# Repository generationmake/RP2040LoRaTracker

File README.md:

# RP2040LoRaTracker
Tracker with a Raspberry Pi RP2040, an AI-Thinker Ra-01 LoRa Module and an u-Blox GNSS receiver

## Firmware
* [ArduinoLoRaAPRSTracker](https://github.com/generationmake/ArduinoLoRaAPRSTracker): This is the default firmware for this board. It enables all basic functions as a ham radio LoRaAPRSTracker

## Antennas

### LoRa antenna (AE1)

SMA connector, 50 Ohm, for 433 MHz LoRa antenna.

### GNSS antenna (AE2)

U.FL connector, 50 Ohm, for GNSS antenna.

## Pinout

### USB (J1)

Micro-USB connector, connected to the RP2040 ant to charge the battery.

### I2C (J2)

compatible to the Sparkfun qwiic standard (https://www.sparkfun.com/qwiic). JST SH 1mm 4-pin.

| pin number | signal        |
|:----------:|:-------------:|
| 1          | GND           |
| 2          | +3V3          |
| 3          | I2C_SDA       |
| 4          | I2C_SCL       |

## Switches

### Reset (SW1)

push button to reset RP2040.

### Boot (SW2)

push button to set RP2040 to boot mode.

### on/off (SW3)

sliding switch to power board from battery.

## enclosure

There exists a 3D printable enclosure to encapsulate the PCB.

## PCB

### Top

### Bottom

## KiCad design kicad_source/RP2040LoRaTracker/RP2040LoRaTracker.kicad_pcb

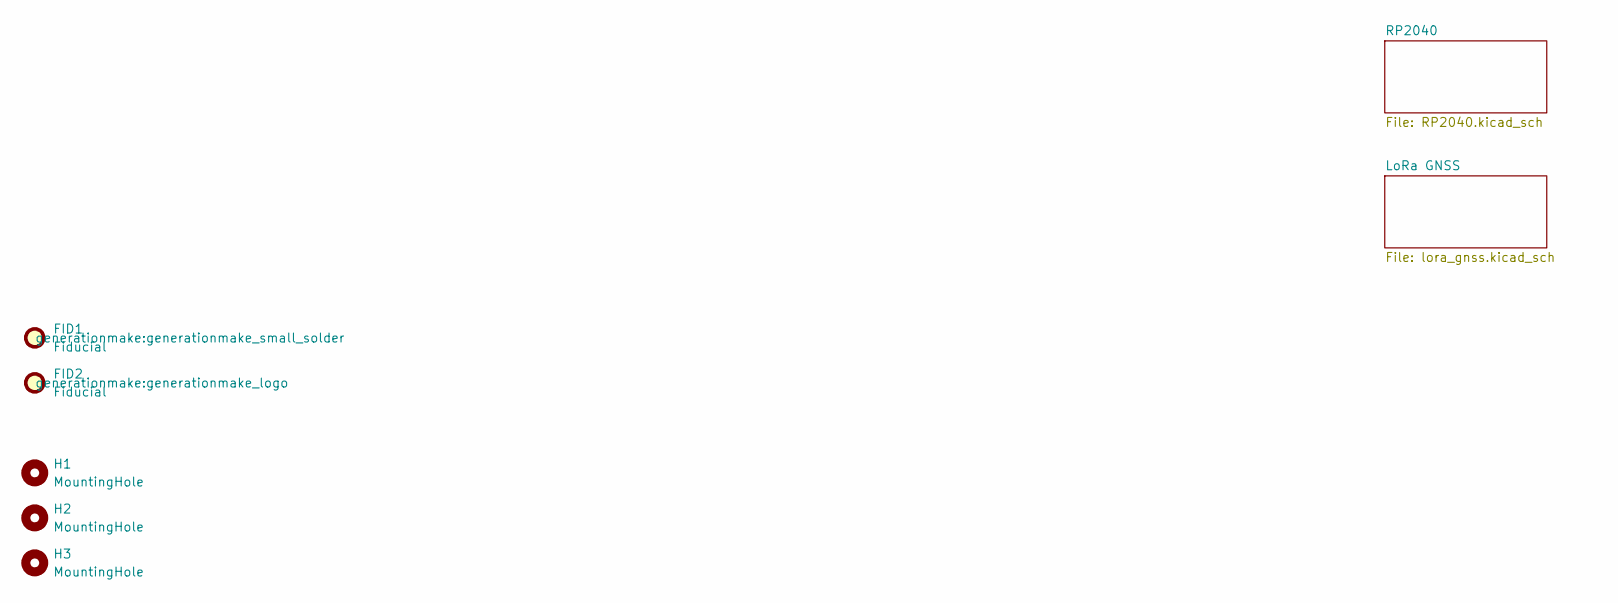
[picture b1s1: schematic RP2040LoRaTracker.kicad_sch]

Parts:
FID1: Fiducial; generationmake_small_solder
FID2: Fiducial; generationmake_logo
H1, H2, H3: MountingHole; MountingHole_2.2mm_M2

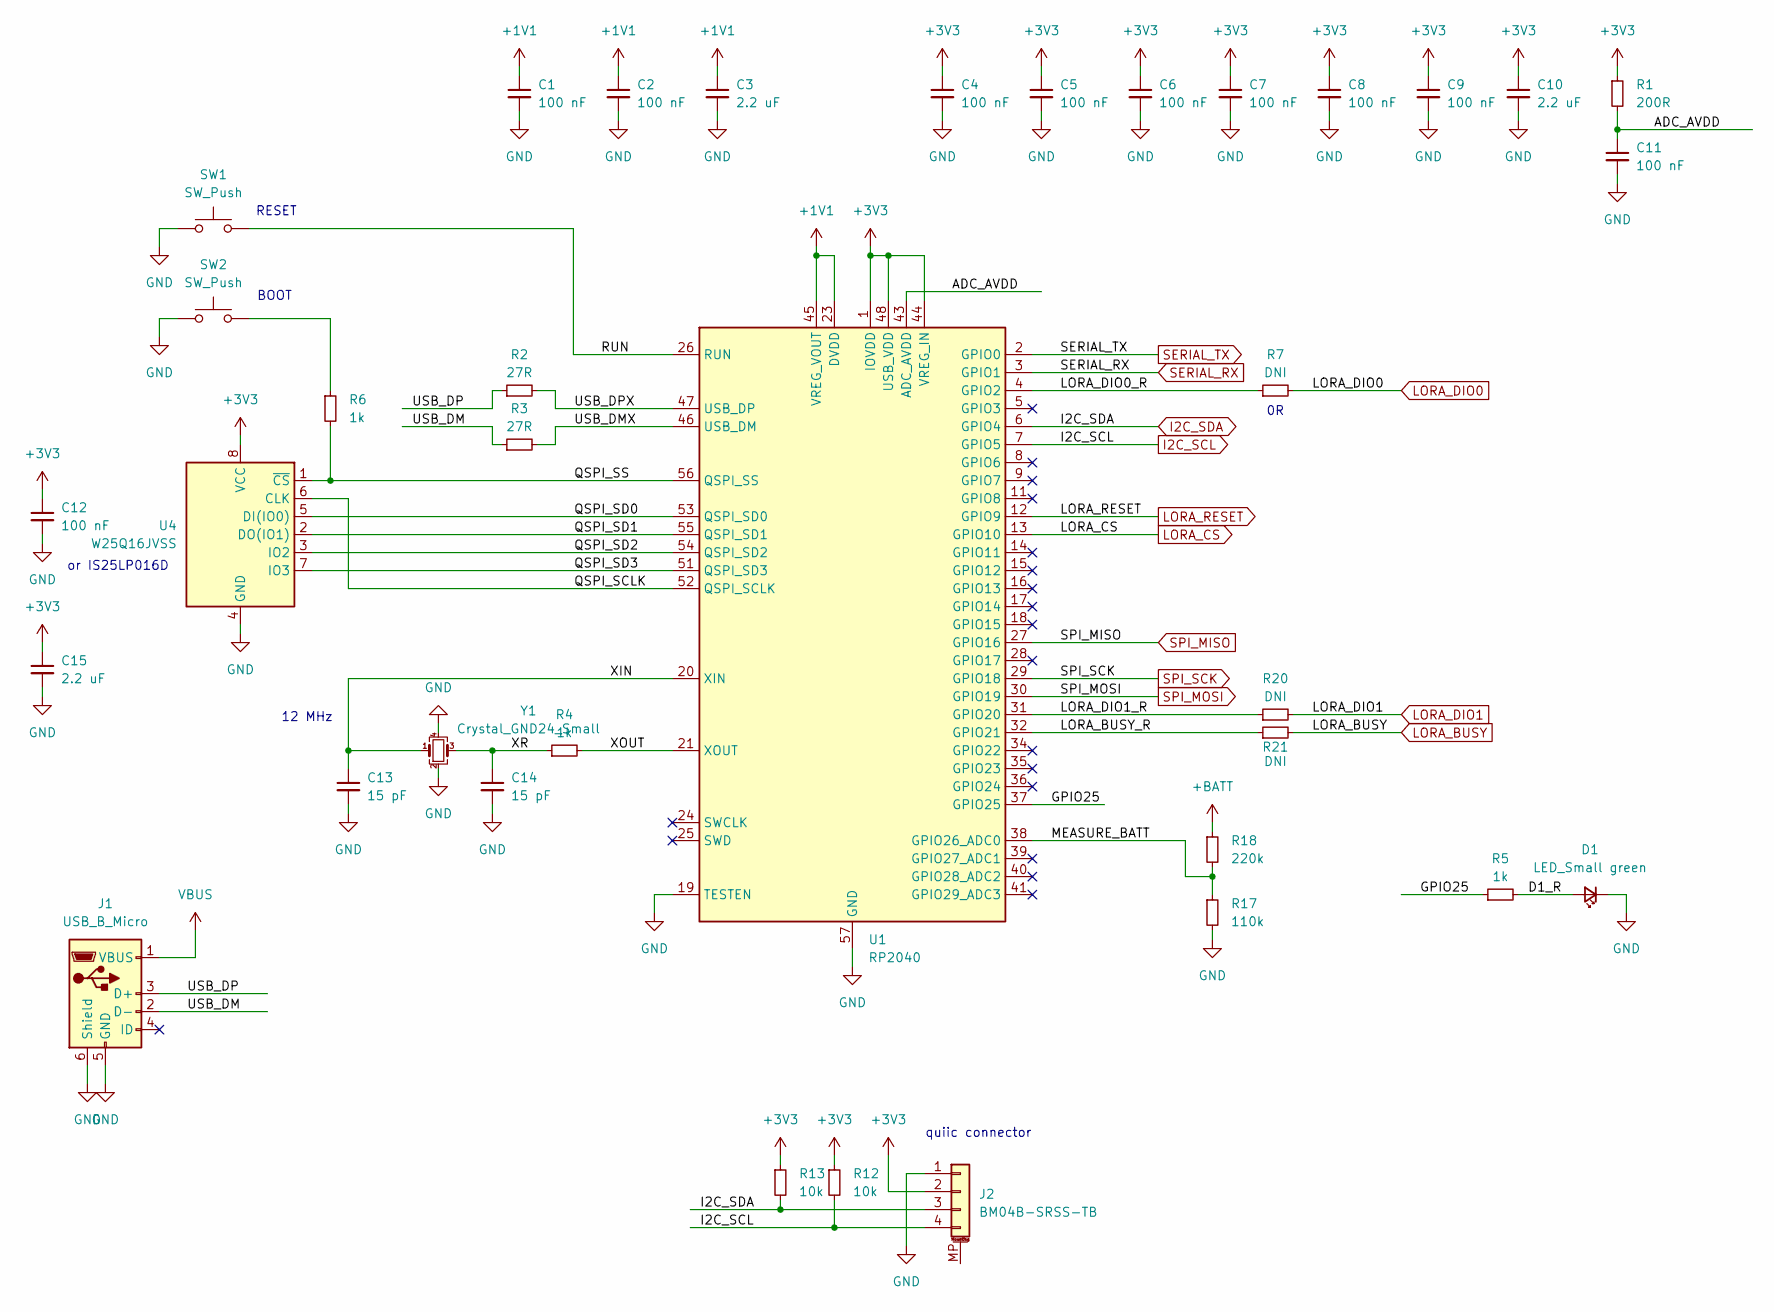
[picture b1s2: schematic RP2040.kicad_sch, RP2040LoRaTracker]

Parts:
C1, C2, C4, C5, C6, C7, C8, C9, C11, C12: 100 nF; C_0603_1608Metric
C3, C10, C15: 2.2 uF; C_0603_1608Metric
C13, C14: 15 pF; C_0603_1608Metric
D1: LED_Small green; LED_0603_1608Metric
J1: USB_B_Micro; USB_Micro-B_Molex_47346-0001
J2: BM04B-SRSS-TB; JST_SH_BM04B-SRSS-TB_1x04-1MP_P1.00mm_Vertical
R1: 200R; R_0603_1608Metric
R2, R3: 27R; R_0603_1608Metric
R4, R5, R6: 1k; R_0603_1608Metric
R7, R20, R21: DNI; R_0603_1608Metric
R12, R13: 10k; R_0603_1608Metric
R17: 110k; R_0603_1608Metric
R18: 220k; R_0603_1608Metric
SW1, SW2: SW_Push; SW_Tactile_SPST_NO_Straight_CK_PTS636Sx25SMTRLFS
U1: RP2040; QFN-56-1EP_7x7mm_P0.4mm_EP3.2x3.2mm
U4: W25Q16JVSS; SOIC-8_5.275x5.275mm_P1.27mm
Y1: Crystal_GND24_Small; Crystal_SMD_3225-4Pin_3.2x2.5mm

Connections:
+1V1: C1.1, C2.1, C3.1, U1.23 (DVDD), U1.45 (VREG_VOUT), U1.50 (DVDD)
+3V3: C4.1, C5.1, C6.1, C7.1, C8.1, C9.1, C10.1, C12.1, C15.1, J2.2, R1.1, R12.1, R13.1, U1.1 (IOVDD), U1.10 (IOVDD), U1.22 (IOVDD), U1.33 (IOVDD), U1.42 (IOVDD), U1.44 (VREG_IN), U1.48 (USB_VDD), U1.49 (IOVDD), U4.8 (VCC); also elsewhere on the board
+BATT: R18.1; also elsewhere on the board
/RP2040/ADC_AVDD: C11.1, R1.2, U1.43 (ADC_AVDD)
/RP2040/D1_R: D1.2 (A), R5.2
/RP2040/GPIO25: R5.1, U1.37 (GPIO25)
/RP2040/LORA_BUSY_R: R21.1, U1.32 (GPIO21)
/RP2040/LORA_DIO0_R: R7.1, U1.4 (GPIO2)
/RP2040/LORA_DIO1_R: R20.1, U1.31 (GPIO20)
/RP2040/MEASURE_BATT: R17.1, R18.2, U1.38 (GPIO26_ADC0)
/RP2040/QSPI_SCLK: U1.52 (QSPI_SCLK), U4.6 (CLK)
/RP2040/QSPI_SD0: U1.53 (QSPI_SD0), U4.5 (DI(IO0))
/RP2040/QSPI_SD1: U1.55 (QSPI_SD1), U4.2 (DO(IO1))
/RP2040/QSPI_SD2: U1.54 (QSPI_SD2), U4.3 (IO2)
/RP2040/QSPI_SD3: U1.51 (QSPI_SD3), U4.7 (IO3)
/RP2040/QSPI_SS: R6.2, U1.56 (QSPI_SS), U4.1 (~CS)
/RP2040/RUN: SW1.2, U1.26 (RUN)
/RP2040/USB_DM: J1.2 (D-), R3.1
/RP2040/USB_DMX: R3.2, U1.46 (USB_DM)
/RP2040/USB_DP: J1.3 (D+), R2.1
/RP2040/USB_DPX: R2.2, U1.47 (USB_DP)
/RP2040/XIN: C13.1, U1.20 (XIN), Y1.1
/RP2040/XOUT: R4.2, U1.21 (XOUT)
/RP2040/XR: C14.1, R4.1, Y1.3
GND: C1.2, C2.2, C3.2, C4.2, C5.2, C6.2, C7.2, C8.2, C9.2, C10.2, C11.2, C12.2, C13.2, C14.2, C15.2, D1.1 (K), J1.5 (GND), J1.6 (Shield), J2.1, R17.2, SW1.1, SW2.1, U1.19 (TESTEN), U1.57 (GND), U4.4 (GND), Y1.2, Y1.4; also elsewhere on the board
I2C_SCL: J2.4, R12.2, U1.7 (GPIO5); also elsewhere on the board
I2C_SDA: J2.3, R13.2, U1.6 (GPIO4); also elsewhere on the board
LORA_BUSY: R21.2; also elsewhere on the board
LORA_CS: U1.13 (GPIO10); also elsewhere on the board
LORA_DIO0: R7.2; also elsewhere on the board
LORA_DIO1: R20.2; also elsewhere on the board
LORA_RESET: U1.12 (GPIO9); also elsewhere on the board
unnamed: R6.1, SW2.2
SERIAL_RX: U1.3 (GPIO1); also elsewhere on the board
SERIAL_TX: U1.2 (GPIO0); also elsewhere on the board
SPI_MISO: U1.27 (GPIO16); also elsewhere on the board
SPI_MOSI: U1.30 (GPIO19); also elsewhere on the board
SPI_SCK: U1.29 (GPIO18); also elsewhere on the board
VBUS: J1.1 (VBUS); also elsewhere on the board

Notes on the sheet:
12 MHz
or IS25LP016D
quiic connector
BOOT
RESET

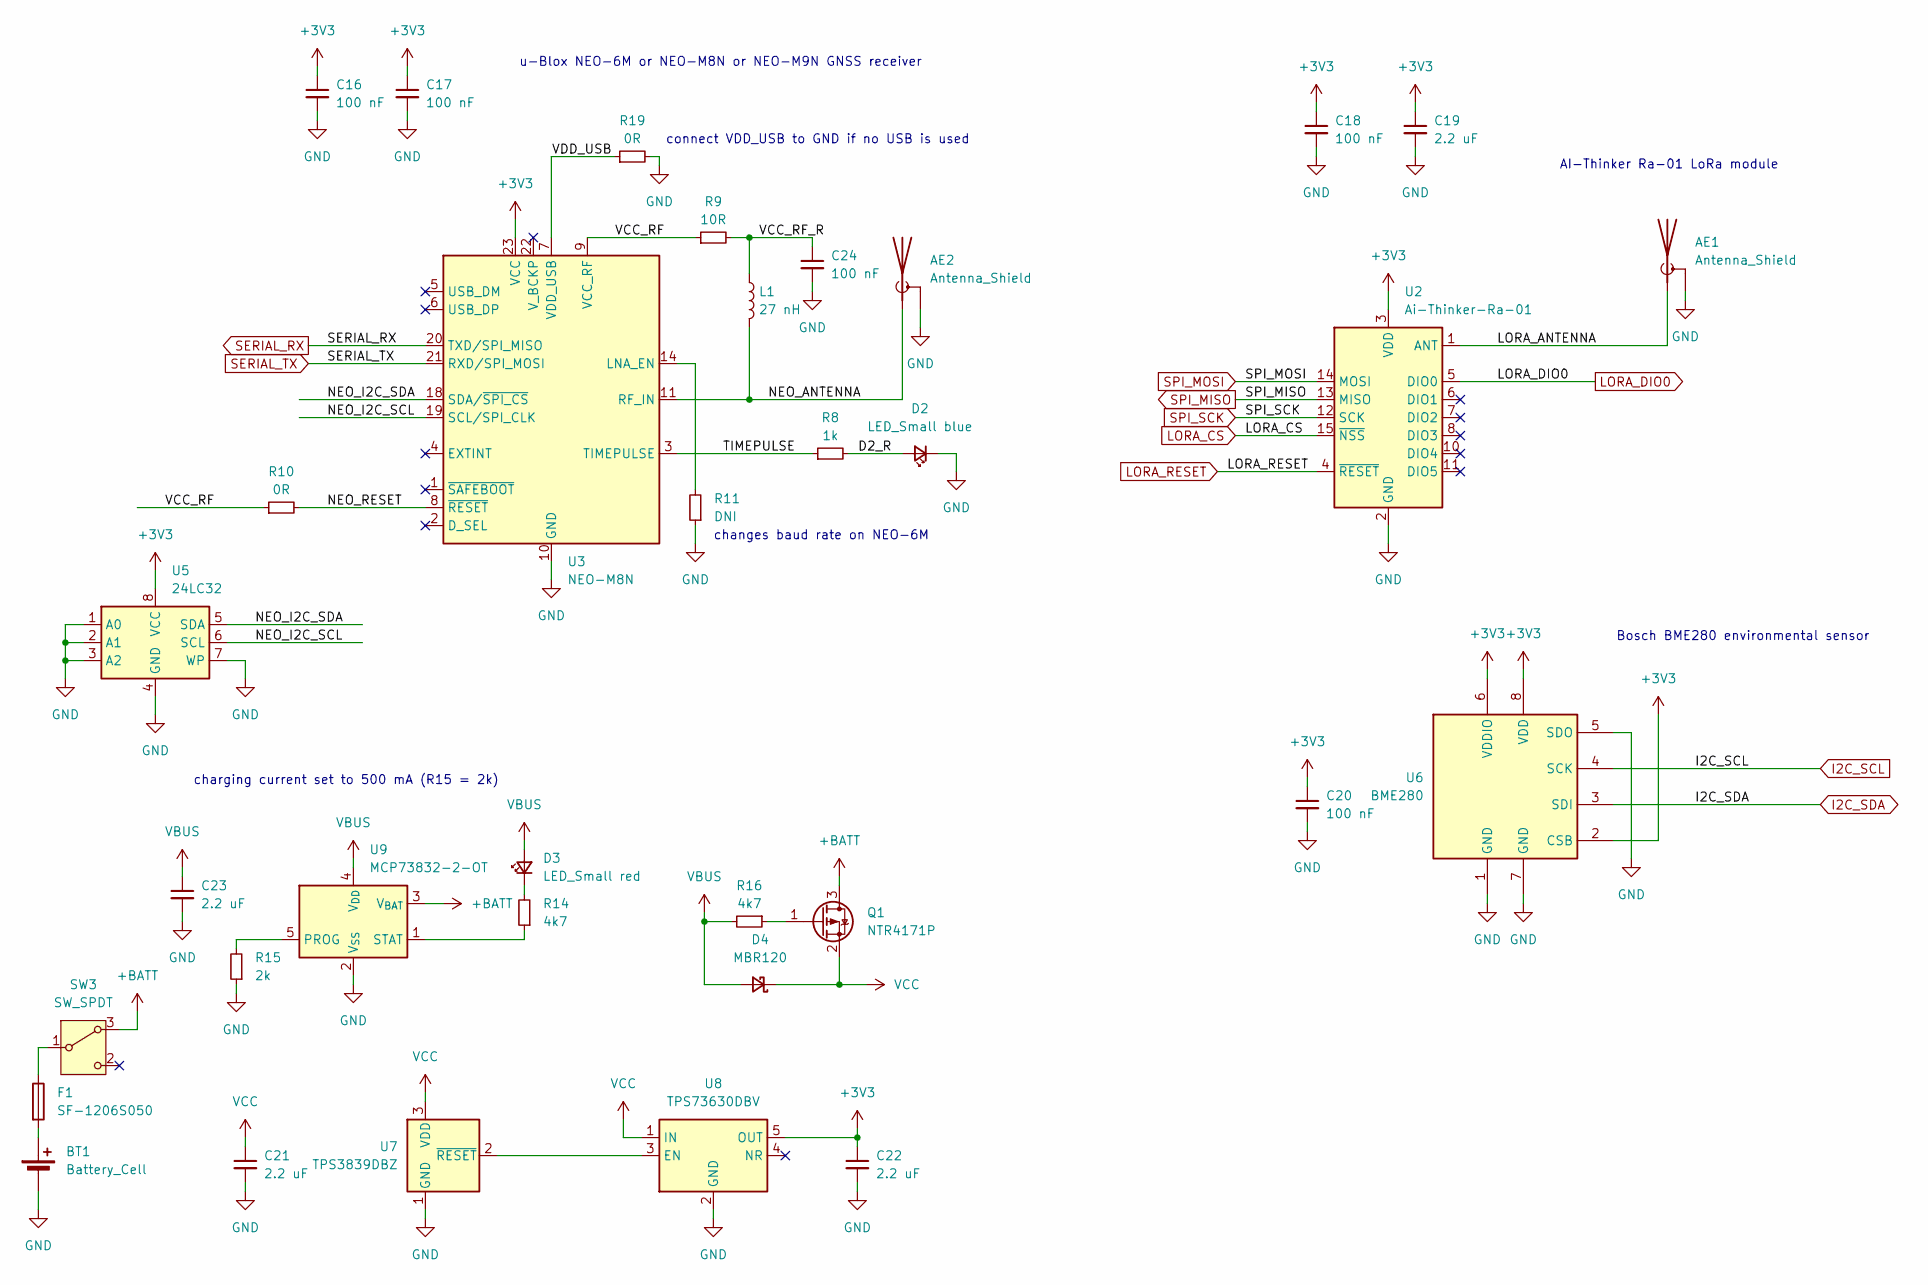
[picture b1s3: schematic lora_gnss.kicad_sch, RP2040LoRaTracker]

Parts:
AE1: Antenna_Shield; SMA_Amphenol_132289_EdgeMount
AE2: Antenna_Shield; U.FL_Hirose_U.FL-R-SMT-1_Vertical
BT1: Battery_Cell; KEYSTONE_1043
C16, C17, C18, C20, C24: 100 nF; C_0603_1608Metric
C19, C21, C22, C23: 2.2 uF; C_0603_1608Metric
D2: LED_Small blue; LED_0603_1608Metric
D3: LED_Small red; LED_0603_1608Metric
D4: MBR120; D_SOD-123
F1: SF-1206S050; Fuse_1206_3216Metric
L1: 27 nH; L_0805_2012Metric
Q1: NTR4171P; SOT-23
R8: 1k; R_0603_1608Metric
R9: 10R; R_0603_1608Metric
R10, R19: 0R; R_0603_1608Metric
R11: DNI; R_0603_1608Metric
R14, R16: 4k7; R_0603_1608Metric
R15: 2k; R_0603_1608Metric
SW3: SW_SPDT; SW_Slide-03_Wuerth-WS-SLTV_10x2.5x6.4_P2.54mm
U2: Ai-Thinker-Ra-01; Ai-Thinker-Ra-01-LoRa
U3: NEO-M8N; ublox_NEO
U5: 24LC32; TSSOP-8_4.4x3mm_P0.65mm
U6: BME280; Bosch_LGA-8_2.5x2.5mm_P0.65mm_ClockwisePinNumbering
U7: TPS3839DBZ; SOT-23
U8: TPS73630DBV; SOT-23-5
U9: MCP73832-2-OT; SOT-23-5

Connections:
+3V3: C16.1, C17.1, C18.1, C19.1, C20.1, C22.1, U2.3 (VDD), U3.23 (VCC), U5.8 (VCC), U6.2 (CSB), U6.6 (VDDIO), U6.8 (VDD), U8.5 (OUT); also elsewhere on the board
+BATT: Q1.3 (D), SW3.3 (A), U9.3 (V_{BAT}); also elsewhere on the board
/LoRa GNSS/D2_R: D2.2 (A), R8.2
/LoRa GNSS/LORA_ANTENNA: AE1.1 (A), U2.1 (ANT)
/LoRa GNSS/NEO_ANTENNA: AE2.1 (A), L1.2, U3.11 (RF_IN)
/LoRa GNSS/NEO_I2C_SCL: U3.19 (SCL/SPI_CLK), U5.6 (SCL)
/LoRa GNSS/NEO_I2C_SDA: U3.18 (SDA/~SPI_CS), U5.5 (SDA)
/LoRa GNSS/NEO_RESET: R10.2, U3.8 (~RESET)
/LoRa GNSS/TIMEPULSE: R8.1, U3.3 (TIMEPULSE)
/LoRa GNSS/VCC_RF: R9.1, R10.1, U3.9 (VCC_RF)
/LoRa GNSS/VCC_RF_R: C24.1, L1.1, R9.2
/LoRa GNSS/VDD_USB: R19.1, U3.7 (VDD_USB)
GND: AE1.2 (Shield), AE2.2 (Shield), BT1.2 (-), C16.2, C17.2, C18.2, C19.2, C20.2, C21.2, C22.2, C23.2, C24.2, D2.1 (K), R11.1, R15.1, R19.2, U2.2 (GND), U2.9 (GND), U2.16 (GND), U3.10 (GND), U3.12 (GND), U3.13 (GND), U3.24 (GND), U5.1 (A0), U5.2 (A1), U5.3 (A2), U5.4 (GND), U5.7 (WP), U6.1 (GND), U6.5 (SDO), U6.7 (GND), U7.1 (GND), U8.2 (GND), U9.2 (V_{SS}); also elsewhere on the board
I2C_SCL: U6.4 (SCK); also elsewhere on the board
I2C_SDA: U6.3 (SDI); also elsewhere on the board
LORA_BUSY: U2.10 (BUSY/DIO4); also elsewhere on the board
LORA_CS: U2.15 (~NSS); also elsewhere on the board
LORA_DIO0: U2.5 (TXEN/DIO0); also elsewhere on the board
LORA_DIO1: U2.6 (DIO1); also elsewhere on the board
LORA_RESET: U2.4 (~RESET); also elsewhere on the board
unnamed: BT1.1 (+), F1.2
unnamed: D3.1 (K), R14.2
unnamed: Q1.1 (G), R16.1
unnamed: F1.1, SW3.1 (B)
unnamed: R11.2, U3.14 (LNA_EN)
unnamed: U7.2 (~RESET), U8.3 (EN)
unnamed: R15.2, U9.5 (PROG)
unnamed: R14.1, U9.1 (STAT)
SERIAL_RX: U3.20 (TXD/SPI_MISO); also elsewhere on the board
SERIAL_TX: U3.21 (RXD/SPI_MOSI); also elsewhere on the board
SPI_MISO: U2.13 (MISO); also elsewhere on the board
SPI_MOSI: U2.14 (MOSI); also elsewhere on the board
SPI_SCK: U2.12 (SCK); also elsewhere on the board
VBUS: C23.1, D3.2 (A), D4.2 (A), R16.2, U9.4 (V_{DD}); also elsewhere on the board
VCC: C21.1, D4.1 (K), Q1.2 (S), U7.3 (VDD), U8.1 (IN)

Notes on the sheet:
changes baud rate on NEO-6M
u-Blox NEO-6M or NEO-M8N or NEO-M9N GNSS receiver
charging current set to 500 mA (R15 = 2k)
connect VDD_USB to GND if no USB is used
Bosch BME280 environmental sensor
AI-Thinker Ra-01 LoRa module

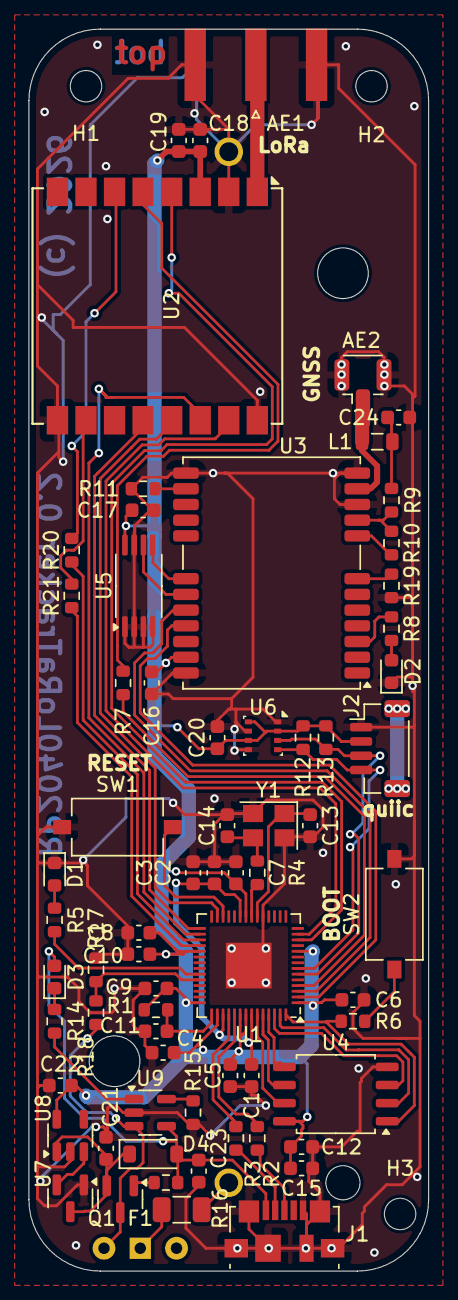
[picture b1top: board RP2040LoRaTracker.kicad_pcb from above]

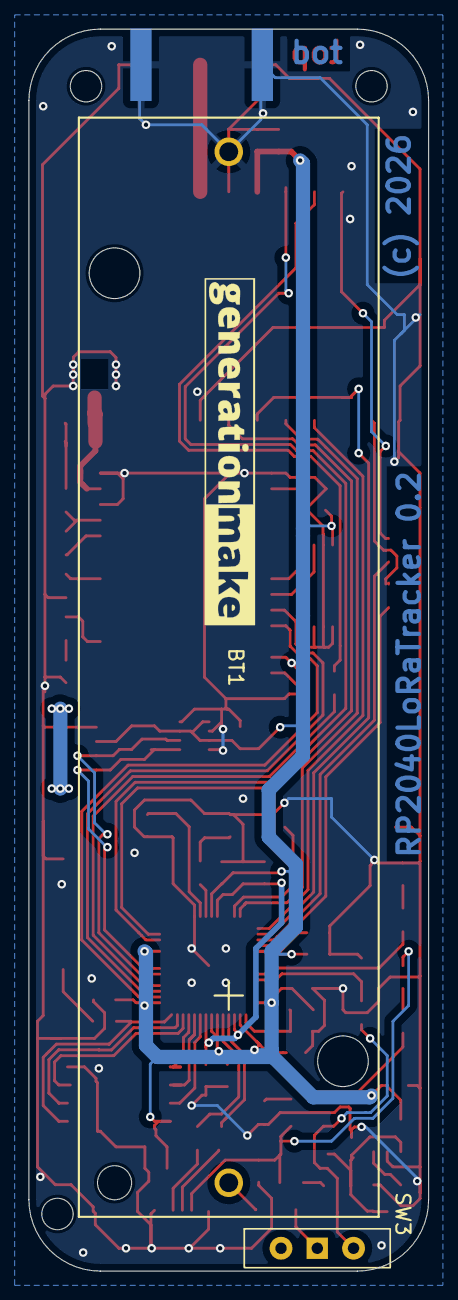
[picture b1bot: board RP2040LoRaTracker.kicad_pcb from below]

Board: 2 copper layers, 28.0 x 87.0 mm, 75 parts (3 on the bottom side), 58 nets.

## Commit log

2025-03-31 started schematic
2025-03-31 started layout
2025-03-31 added BME280 and quiic connector
2025-03-31 added voltage regulator
2025-03-31 added battery charger
2025-03-31 added schematic pdf
2025-03-31 changed battery holder, updated layout
2025-04-01 beautified layout, made DRC
2025-04-20 updated some values in schematic, added comments, updated schematic pdf
2025-04-20 added images
2025-05-04 set charging current to 500 mA (R15=2k)
2025-09-08 added workflows
2025-09-08 fixed spelling
2025-09-09 updated some 3d models in footprints
2025-09-09 fixed all 3d models in footprints
2025-09-09 updated rendering
2025-09-09 added step file
2025-09-09 added freecad project
2025-09-09 added enclosure, added top part
2025-09-09 generated stl files
2025-10-27 Bump actions/download-artifact from 5 to 6
    Bumps [actions/download-artifact](https://github.com/actions/download-artifact) from 5 to 6.
    - [Release notes](https://github.com/actions/download-artifact/releases)
    - [Commits](https://github.com/actions/download-artifact/compare/v5...v6)
    ---
    updated-dependencies:
    - dependency-name: actions/download-artifact
2025-10-27 Bump actions/upload-artifact from 4 to 5
    Bumps [actions/upload-artifact](https://github.com/actions/upload-artifact) from 4 to 5.
    - [Release notes](https://github.com/actions/upload-artifact/releases)
    - [Commits](https://github.com/actions/upload-artifact/compare/v4...v5)
    ---
    updated-dependencies:
    - dependency-name: actions/upload-artifact
2025-11-09 updated formatting checks, tried to ignore step file
2025-11-09 updated readme, added image of enclusore
2025-11-21 Bump actions/checkout from 5 to 6
    Bumps [actions/checkout](https://github.com/actions/checkout) from 5 to 6.
    - [Release notes](https://github.com/actions/checkout/releases)
    - [Changelog](https://github.com/actions/checkout/blob/main/CHANGELOG.md)
    - [Commits](https://github.com/actions/checkout/compare/v5...v6)
    ---
    updated-dependencies:
2025-12-15 Bump actions/download-artifact from 6 to 7
    Bumps [actions/download-artifact](https://github.com/actions/download-artifact) from 6 to 7.
    - [Release notes](https://github.com/actions/download-artifact/releases)
    - [Commits](https://github.com/actions/download-artifact/compare/v6...v7)
    ---
    updated-dependencies:
    - dependency-name: actions/download-artifact
2025-12-15 Bump actions/upload-artifact from 5 to 6
    Bumps [actions/upload-artifact](https://github.com/actions/upload-artifact) from 5 to 6.
    - [Release notes](https://github.com/actions/upload-artifact/releases)
    - [Commits](https://github.com/actions/upload-artifact/compare/v5...v6)
    ---
    updated-dependencies:
    - dependency-name: actions/upload-artifact
2026-02-27 Bump actions/download-artifact from 7 to 8
    Bumps [actions/download-artifact](https://github.com/actions/download-artifact) from 7 to 8.
    - [Release notes](https://github.com/actions/download-artifact/releases)
    - [Commits](https://github.com/actions/download-artifact/compare/v7...v8)
    ---
    updated-dependencies:
    - dependency-name: actions/download-artifact
2026-02-27 Bump actions/upload-artifact from 6 to 7
    Bumps [actions/upload-artifact](https://github.com/actions/upload-artifact) from 6 to 7.
    - [Release notes](https://github.com/actions/upload-artifact/releases)
    - [Commits](https://github.com/actions/upload-artifact/compare/v6...v7)
    ---
    updated-dependencies:
    - dependency-name: actions/upload-artifact
2026-03-16 Bump geekyeggo/delete-artifact from 5 to 6
    Bumps [geekyeggo/delete-artifact](https://github.com/geekyeggo/delete-artifact) from 5 to 6.
    - [Release notes](https://github.com/geekyeggo/delete-artifact/releases)
    - [Changelog](https://github.com/GeekyEggo/delete-artifact/blob/main/CHANGELOG.md)
    - [Commits](https://github.com/geekyeggo/delete-artifact/compare/v5...v6)
    ---
    updated-dependencies:
2026-04-13 Bump carlosperate/download-file-action from 2.0.2 to 2.0.3
    Bumps [carlosperate/download-file-action](https://github.com/carlosperate/download-file-action) from 2.0.2 to 2.0.3.
    - [Release notes](https://github.com/carlosperate/download-file-action/releases)
    - [Commits](https://github.com/carlosperate/download-file-action/compare/v2.0.2...v2.0.3)
    ---
    updated-dependencies:
    - dependency-name: carlosperate/download-file-action
2026-05-30 added battery voltage measurement, R17 and R18
2026-05-30 added compatibility for u-blox NEO-M9N, added R19 and C24
2026-05-30 added compatibility for LoRa module Ra-01S, added R20 and R21
2026-06-19 Bump actions/checkout from 6 to 7
    Bumps [actions/checkout](https://github.com/actions/checkout) from 6 to 7.
    - [Release notes](https://github.com/actions/checkout/releases)
    - [Changelog](https://github.com/actions/checkout/blob/main/CHANGELOG.md)
    - [Commits](https://github.com/actions/checkout/compare/v6...v7)
    ---
    updated-dependencies:

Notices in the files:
kicad_source/RP2040LoRaTracker/RP2040LoRaTracker.kicad_pcb:
(c) 2026
